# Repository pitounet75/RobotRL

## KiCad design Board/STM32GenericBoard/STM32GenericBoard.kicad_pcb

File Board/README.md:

# Robot PCB (KiCad)

KiCad projects for the RobotRL hardware.

## STM32GenericBoard

| Item | Value |
|------|--------|
| MCU (schematic) | **STM32H743VGTx** (LQFP100) — matches firmware `STM32H743VIT6` in [`RobotSTM32FirmWare.ioc`](../STM32/RobotSTM32FirmWare/RobotSTM32FirmWare.ioc) |
| IMU symbol | TDK **ICM-45686** (local lib under `libs/ICM_45686/`) |
| Status | Schematic in progress — **no routed PCB** yet (empty `.kicad_pcb`) |

### Open in KiCad

1. Open `STM32GenericBoard/STM32GenericBoard.kicad_pro`.
2. Assign footprints and complete power + bus wiring (FDCAN2, SPI1, USART, SWD).
3. Cross-check nets against CubeMX: [`STM32/RobotSTM32FirmWare/README.md`](../STM32/RobotSTM32FirmWare/README.md).

### Pin map (firmware reference)

Application CAN uses **FDCAN2** (PB12 RX, PB13 TX), not FDCAN1. See firmware README for full USART/SPI table.

### Notes

- Do not commit KiCad lock files (`~*.lck`) — listed in repo `.gitignore`.
- For symbol generation from CubeMX, tools such as [cubemx2kicad](https://github.com/alt-uranium/cubemx2kicad) can label pins from the `.ioc` file.

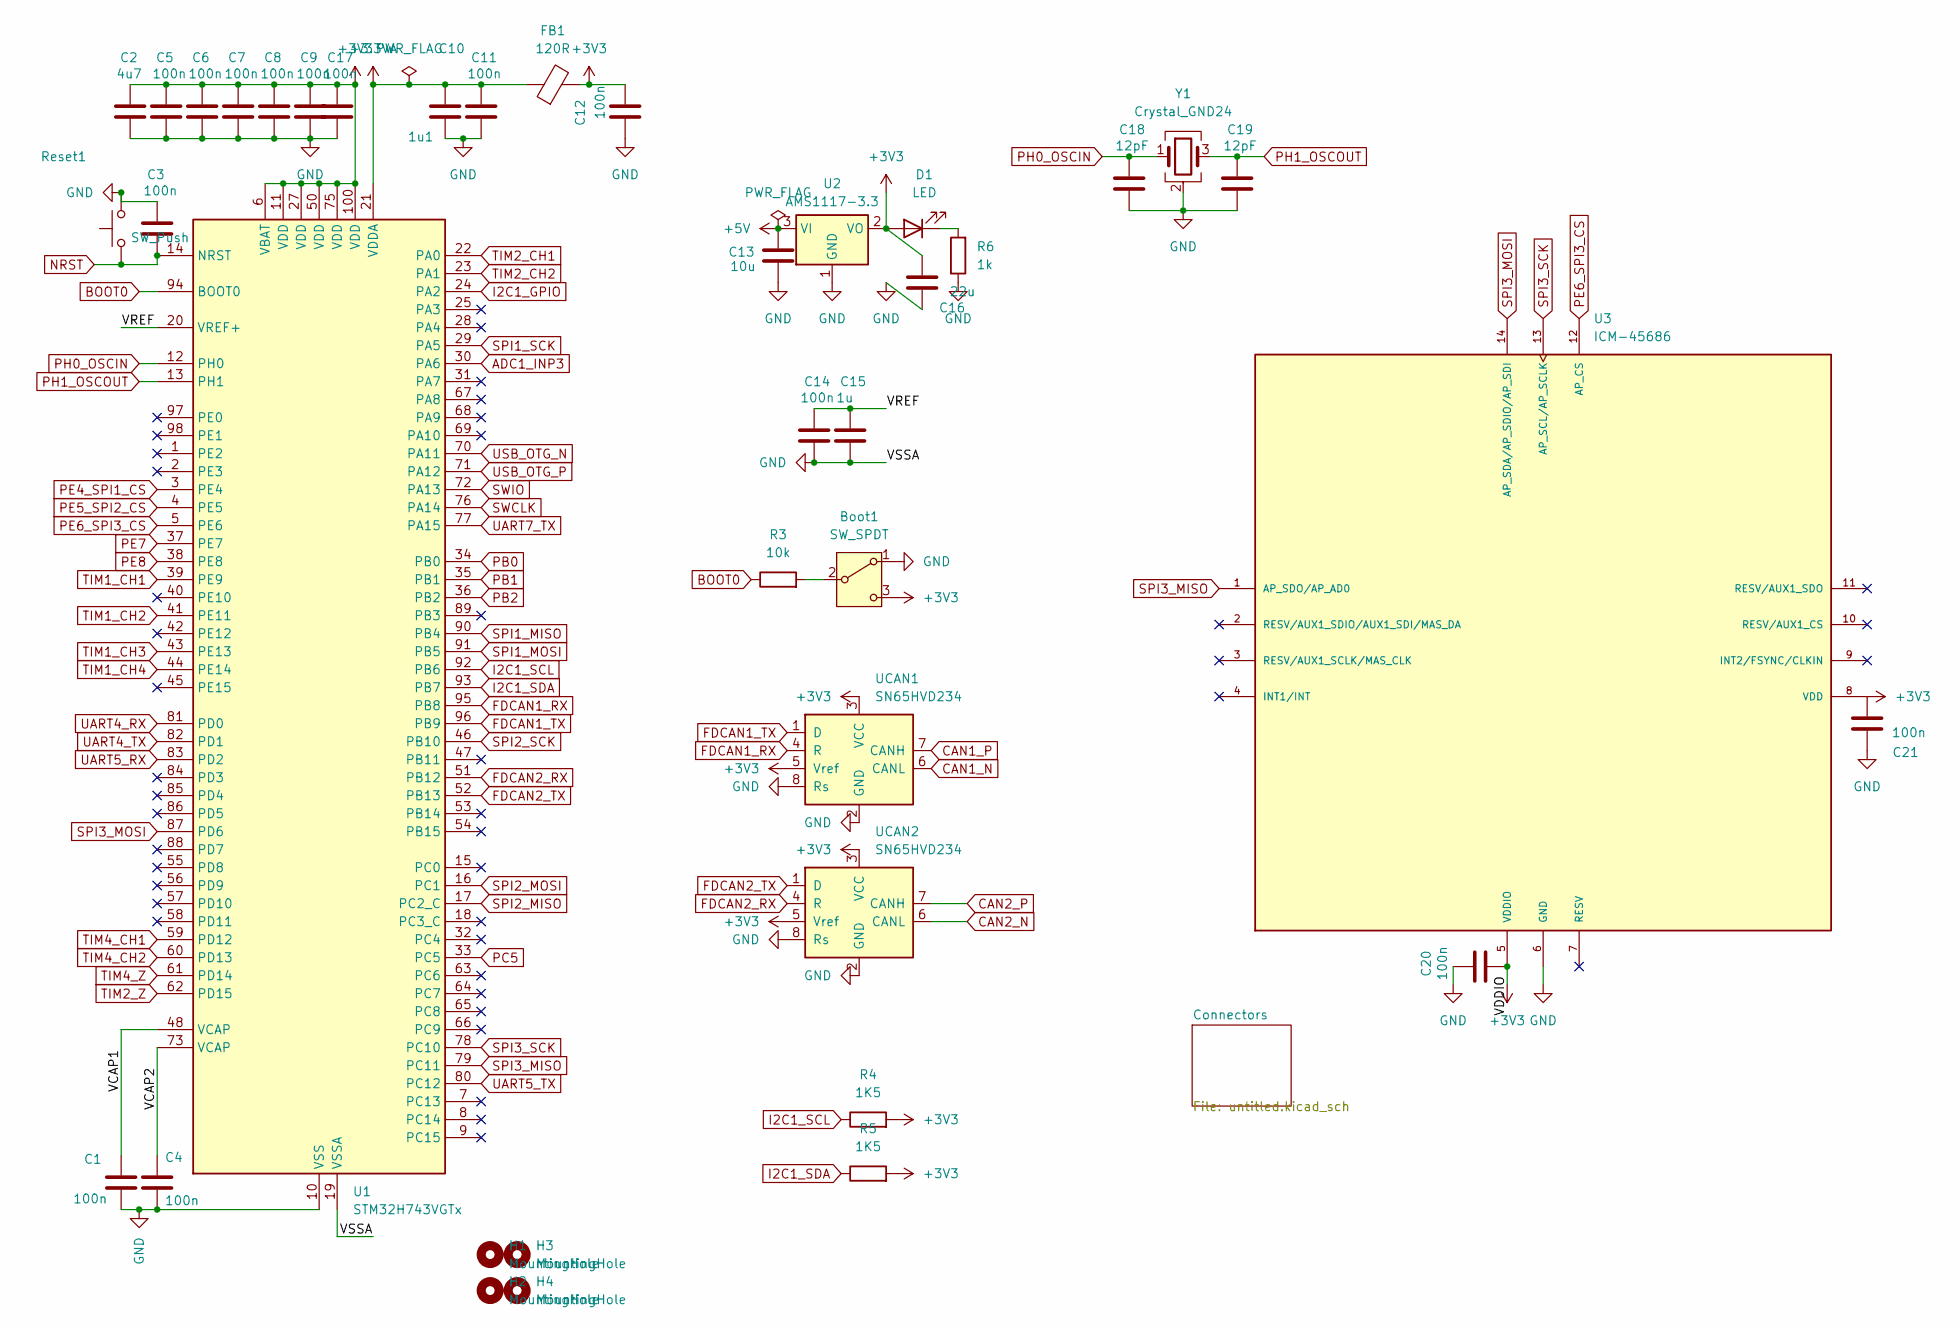
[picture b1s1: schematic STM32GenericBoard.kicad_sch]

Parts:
Boot1: SW_SPDT; SW_SPDT_PCM12
C1, C3, C4, C5, C6, C7, C8, C9, C11, C12, C14, C17, C20, C21: 100n; C_0402_1005Metric_Pad0.74x0.62mm_HandSolder
C2: 4u7; C_0603_1608Metric_Pad1.08x0.95mm_HandSolder
C10: 1u1; C_0603_1608Metric_Pad1.08x0.95mm_HandSolder
C13: 10u; C_0603_1608Metric_Pad1.08x0.95mm_HandSolder
C15: 1u; C_0603_1608Metric_Pad1.08x0.95mm_HandSolder
C16: 22u; C_0805_2012Metric_Pad1.18x1.45mm_HandSolder
C18, C19: 12pF; C_0402_1005Metric_Pad0.74x0.62mm_HandSolder
D1: LED; LED_0805_2012Metric_Pad1.15x1.40mm_HandSolder
FB1: 120R; L_0805_2012Metric_Pad1.05x1.20mm_HandSolder
H1, H2, H3, H4: MountingHole; MountingHole_2.2mm_M2
R3: 10k; R_0402_1005Metric_Pad0.72x0.64mm_HandSolder
R4, R5: 1K5; R_0402_1005Metric_Pad0.72x0.64mm_HandSolder
R6: 1k; R_0402_1005Metric_Pad0.72x0.64mm_HandSolder
Reset1: SW_Push; SW_Push_1P1T_NO_Vertical_Wuerth_434133025816
U1: STM32H743VGTx; LQFP-100_14x14mm_P0.5mm
U2: AMS1117-3.3; SOT-223-3_TabPin2
U3: ICM-45686; IC_ICM-45686; PARTREV 0.2
UCAN1, UCAN2: SN65HVD234; SOIC-8_3.9x4.9mm_P1.27mm
Y1: Crystal_GND24; Crystal_SMD_2520-4Pin_2.5x2.0mm

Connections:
+3.3VA: C10.1, C11.1, FB1.1, U1.21 (VDDA)
+3V3: Boot1.3 (C), C2.1, C5.1, C6.1, C7.1, C8.1, C9.1, C12.2, C16.1, C17.1, C20.2, C21.2, D1.2 (A), FB1.2, R4.2, R5.2, U1.6 (VBAT), U1.11 (VDD), U1.27 (VDD), U1.50 (VDD), U1.75 (VDD), U1.100 (VDD), U2.2 (VO), U3.5 (VDDIO), U3.8 (VDD), UCAN1.3 (VCC), UCAN1.5 (Vref), UCAN2.3 (VCC), UCAN2.5 (Vref); also elsewhere on the board
+5V: C13.1, U2.3 (VI); also elsewhere on the board
/VCAP1: C1.1, U1.48 (VCAP)
/VCAP2: C4.1, U1.73 (VCAP)
/VREF: C14.1, C15.1, U1.20 (VREF+)
ADC1_INP3: U1.30 (PA6); also elsewhere on the board
BOOT0: R3.1, U1.94 (BOOT0)
CAN1_N: UCAN1.6 (CANL); also elsewhere on the board
CAN1_P: UCAN1.7 (CANH); also elsewhere on the board
CAN2_N: UCAN2.6 (CANL); also elsewhere on the board
CAN2_P: UCAN2.7 (CANH); also elsewhere on the board
FDCAN1_RX: U1.95 (PB8), UCAN1.4 (R)
FDCAN1_TX: U1.96 (PB9), UCAN1.1 (D)
FDCAN2_RX: U1.51 (PB12), UCAN2.4 (R)
FDCAN2_TX: U1.52 (PB13), UCAN2.1 (D)
GND: Boot1.1 (A), C1.2, C2.2, C3.1, C4.2, C5.2, C6.2, C7.2, C8.2, C9.2, C10.2, C11.2, C12.1, C13.2, C14.2, C15.2, C16.2, C17.2, C18.2, C19.2, C20.1, C21.1, R6.1, Reset1.2, U1.10 (VSS), U1.19 (VSSA), U1.26 (VSS), U1.49 (VSS), U1.74 (VSS), U1.99 (VSS), U2.1 (GND), U3.6 (GND), UCAN1.2 (GND), UCAN1.8 (Rs), UCAN2.2 (GND), UCAN2.8 (Rs), Y1.2 (G), Y1.4 (G); also elsewhere on the board
I2C1_GPIO: U1.24 (PA2); also elsewhere on the board
I2C1_SCL: R4.1, U1.92 (PB6); also elsewhere on the board
I2C1_SDA: R5.1, U1.93 (PB7); also elsewhere on the board
NRST: C3.2, Reset1.1, U1.14 (NRST); also elsewhere on the board
unnamed: Boot1.2 (B), R3.2
unnamed: D1.1 (K), R6.2
PB0: U1.34 (PB0); also elsewhere on the board
PB1: U1.35 (PB1); also elsewhere on the board
PB2: U1.36 (PB2); also elsewhere on the board
PC5: U1.33 (PC5); also elsewhere on the board
PE4_SPI1_CS: U1.3 (PE4); also elsewhere on the board
PE5_SPI2_CS: U1.4 (PE5); also elsewhere on the board
PE6_SPI3_CS: U1.5 (PE6), U3.12 (AP_CS)
PE7: U1.37 (PE7); also elsewhere on the board
PE8: U1.38 (PE8); also elsewhere on the board
PH0_OSCIN: C18.1, U1.12 (PH0), Y1.1
PH1_OSCOUT: C19.1, U1.13 (PH1), Y1.3
SPI1_MISO: U1.90 (PB4); also elsewhere on the board
SPI1_MOSI: U1.91 (PB5); also elsewhere on the board
SPI1_SCK: U1.29 (PA5); also elsewhere on the board
SPI2_MISO: U1.17 (PC2_C); also elsewhere on the board
SPI2_MOSI: U1.16 (PC1); also elsewhere on the board
SPI2_SCK: U1.46 (PB10); also elsewhere on the board
SPI3_MISO: U1.79 (PC11), U3.1 (AP_SDO/AP_AD0)
SPI3_MOSI: U1.87 (PD6), U3.14 (AP_SDA/AP_SDIO/AP_SDI)
SPI3_SCK: U1.78 (PC10), U3.13 (AP_SCL/AP_SCLK)
SWCLK: U1.76 (PA14); also elsewhere on the board
SWIO: U1.72 (PA13); also elsewhere on the board
TIM1_CH1: U1.39 (PE9); also elsewhere on the board
TIM1_CH2: U1.41 (PE11); also elsewhere on the board
TIM1_CH3: U1.43 (PE13); also elsewhere on the board
TIM1_CH4: U1.44 (PE14); also elsewhere on the board
TIM2_CH1: U1.22 (PA0); also elsewhere on the board
TIM2_CH2: U1.23 (PA1); also elsewhere on the board
TIM2_Z: U1.62 (PD15); also elsewhere on the board
TIM4_CH1: U1.59 (PD12); also elsewhere on the board
TIM4_CH2: U1.60 (PD13); also elsewhere on the board
TIM4_Z: U1.61 (PD14); also elsewhere on the board
UART4_RX: U1.81 (PD0); also elsewhere on the board
UART4_TX: U1.82 (PD1); also elsewhere on the board
UART5_RX: U1.83 (PD2); also elsewhere on the board
UART5_TX: U1.80 (PC12); also elsewhere on the board
UART7_TX: U1.77 (PA15); also elsewhere on the board
USB_OTG_N: U1.70 (PA11); also elsewhere on the board
USB_OTG_P: U1.71 (PA12); also elsewhere on the board

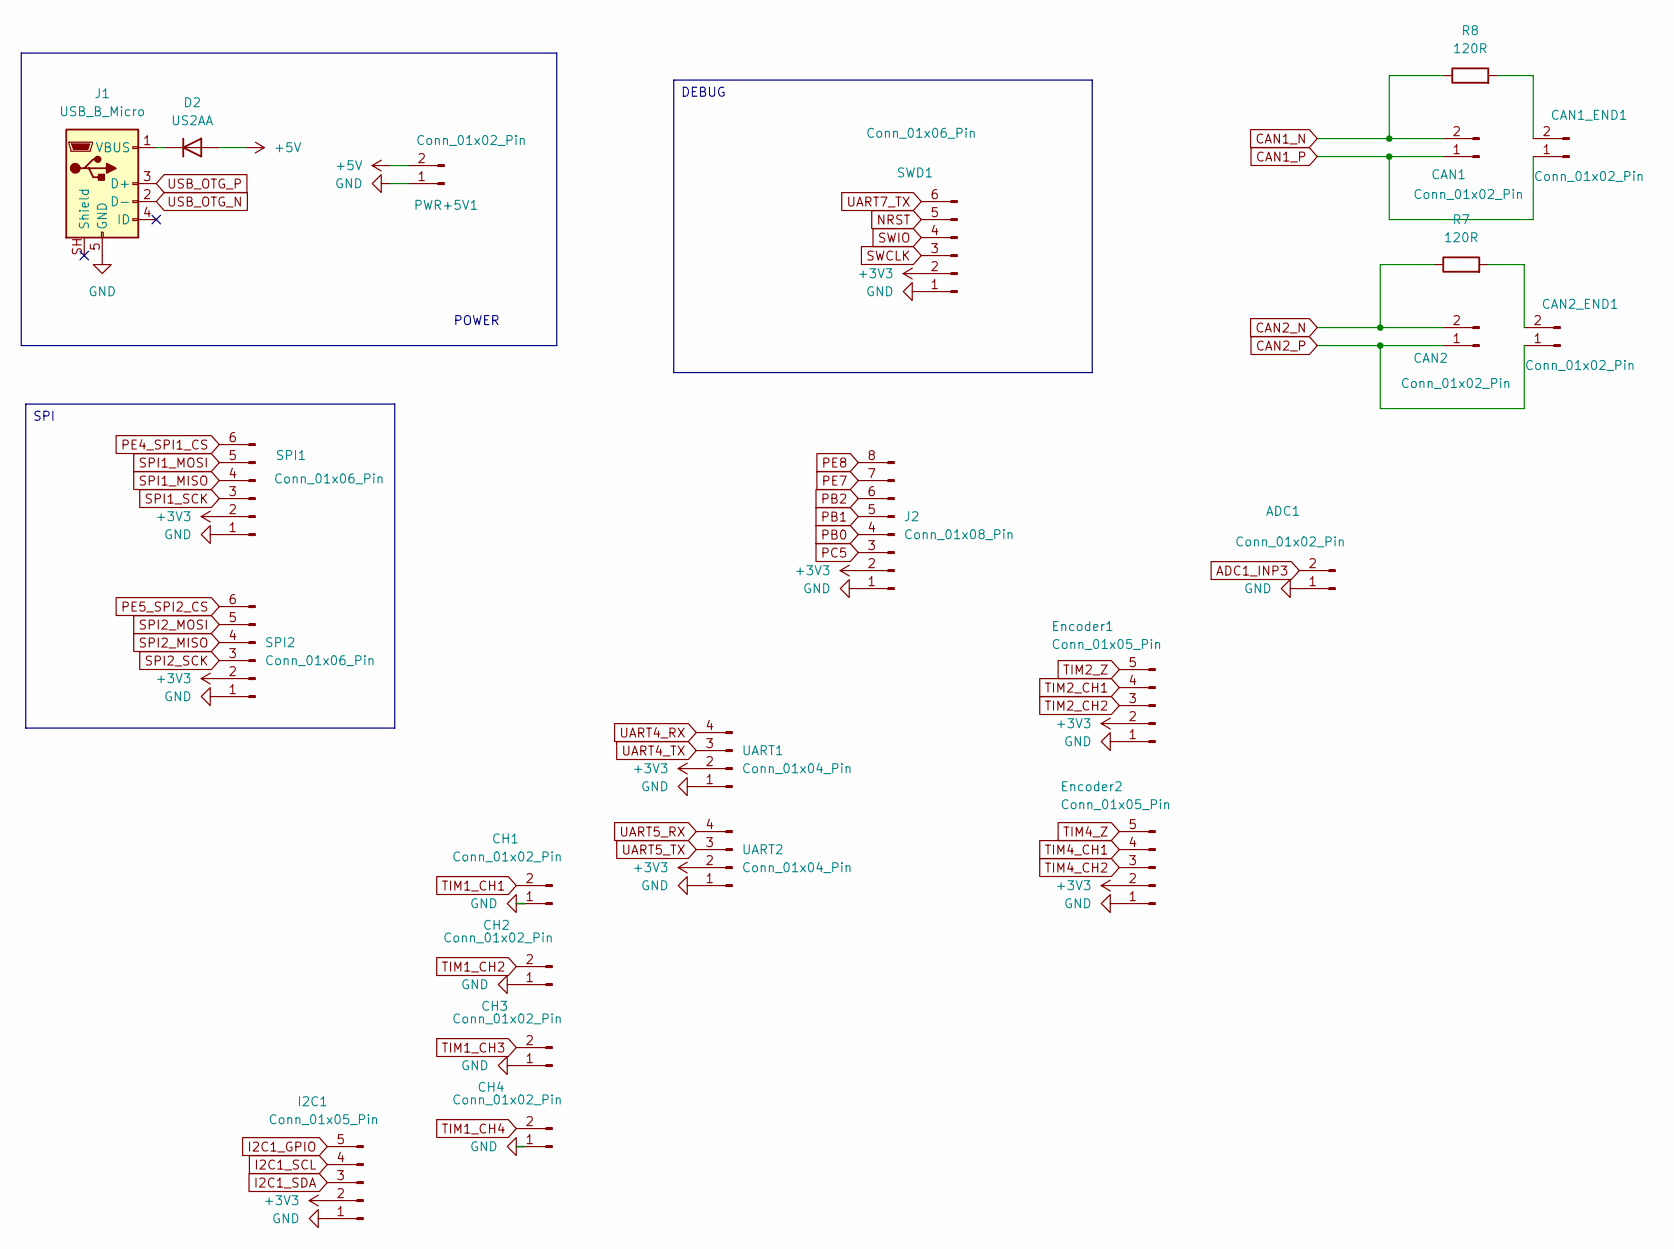
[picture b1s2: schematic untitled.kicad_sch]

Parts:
ADC1: Conn_01x02_Pin; JST_GH_BM02B-GHS-TBT_1x02-1MP_P1.25mm_Vertical
CAN1, CAN2: Conn_01x02_Pin; JST_GH_BM02B-GHS-TBT_1x02-1MP_P1.25mm_Vertical
CAN1_END1, CAN2_END1: Conn_01x02_Pin; PinHeader_1x02_P2.54mm_Vertical
CH1, CH2, CH3, CH4: Conn_01x02_Pin; JST_GH_BM02B-GHS-TBT_1x02-1MP_P1.25mm_Vertical
D2: US2AA; D_SMA
Encoder1, Encoder2: Conn_01x05_Pin; JST_GH_BM05B-GHS-TBT_1x05-1MP_P1.25mm_Vertical
I2C1: Conn_01x05_Pin; JST_GH_BM05B-GHS-TBT_1x05-1MP_P1.25mm_Vertical
J1: USB_B_Micro; USB_Micro-B_Amphenol_10118194-0001LF_Horizontal
J2: Conn_01x08_Pin; JST_GH_BM08B-GHS-TBT_1x08-1MP_P1.25mm_Vertical
PWR+5V1: Conn_01x02_Pin; PinHeader_1x02_P2.54mm_Vertical
R7, R8: 120R; R_0402_1005Metric_Pad0.72x0.64mm_HandSolder
SPI1, SPI2: Conn_01x06_Pin; JST_GH_BM06B-GHS-TBT_1x06-1MP_P1.25mm_Vertical
SWD1: Conn_01x06_Pin; JST_GH_BM06B-GHS-TBT_1x06-1MP_P1.25mm_Vertical
UART1, UART2: Conn_01x04_Pin; JST_GH_BM04B-GHS-TBT_1x04-1MP_P1.25mm_Vertical

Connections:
+3V3: Encoder1.2, Encoder2.2, I2C1.2, J2.2, SPI1.2, SPI2.2, SWD1.2, UART1.2, UART2.2; also elsewhere on the board
+5V: D2.2 (A), PWR+5V1.2; also elsewhere on the board
ADC1_INP3: ADC1.2; also elsewhere on the board
CAN1_N: CAN1.2, R8.1; also elsewhere on the board
CAN1_P: CAN1.1, CAN1_END1.1; also elsewhere on the board
CAN2_N: CAN2.2, R7.1; also elsewhere on the board
CAN2_P: CAN2.1, CAN2_END1.1; also elsewhere on the board
GND: ADC1.1, CH1.1, CH2.1, CH3.1, CH4.1, Encoder1.1, Encoder2.1, I2C1.1, J1.5 (GND), J2.1, PWR+5V1.1, SPI1.1, SPI2.1, SWD1.1, UART1.1, UART2.1; also elsewhere on the board
I2C1_GPIO: I2C1.5; also elsewhere on the board
I2C1_SCL: I2C1.4; also elsewhere on the board
I2C1_SDA: I2C1.3; also elsewhere on the board
NRST: SWD1.5; also elsewhere on the board
unnamed: CAN1_END1.2, R8.2
unnamed: CAN2_END1.2, R7.2
unnamed: D2.1 (K), J1.1 (VBUS)
PB0: J2.4; also elsewhere on the board
PB1: J2.5; also elsewhere on the board
PB2: J2.6; also elsewhere on the board
PC5: J2.3; also elsewhere on the board
PE4_SPI1_CS: SPI1.6; also elsewhere on the board
PE5_SPI2_CS: SPI2.6; also elsewhere on the board
PE7: J2.7; also elsewhere on the board
PE8: J2.8; also elsewhere on the board
SPI1_MISO: SPI1.4; also elsewhere on the board
SPI1_MOSI: SPI1.5; also elsewhere on the board
SPI1_SCK: SPI1.3; also elsewhere on the board
SPI2_MISO: SPI2.4; also elsewhere on the board
SPI2_MOSI: SPI2.5; also elsewhere on the board
SPI2_SCK: SPI2.3; also elsewhere on the board
SWCLK: SWD1.3; also elsewhere on the board
SWIO: SWD1.4; also elsewhere on the board
TIM1_CH1: CH1.2; also elsewhere on the board
TIM1_CH2: CH2.2; also elsewhere on the board
TIM1_CH3: CH3.2; also elsewhere on the board
TIM1_CH4: CH4.2; also elsewhere on the board
TIM2_CH1: Encoder1.4; also elsewhere on the board
TIM2_CH2: Encoder1.3; also elsewhere on the board
TIM2_Z: Encoder1.5; also elsewhere on the board
TIM4_CH1: Encoder2.4; also elsewhere on the board
TIM4_CH2: Encoder2.3; also elsewhere on the board
TIM4_Z: Encoder2.5; also elsewhere on the board
UART4_RX: UART1.4; also elsewhere on the board
UART4_TX: UART1.3; also elsewhere on the board
UART5_RX: UART2.4; also elsewhere on the board
UART5_TX: UART2.3; also elsewhere on the board
UART7_TX: SWD1.6; also elsewhere on the board
USB_OTG_N: J1.2 (D-); also elsewhere on the board
USB_OTG_P: J1.3 (D+); also elsewhere on the board

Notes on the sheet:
POWER
SPI
DEBUG

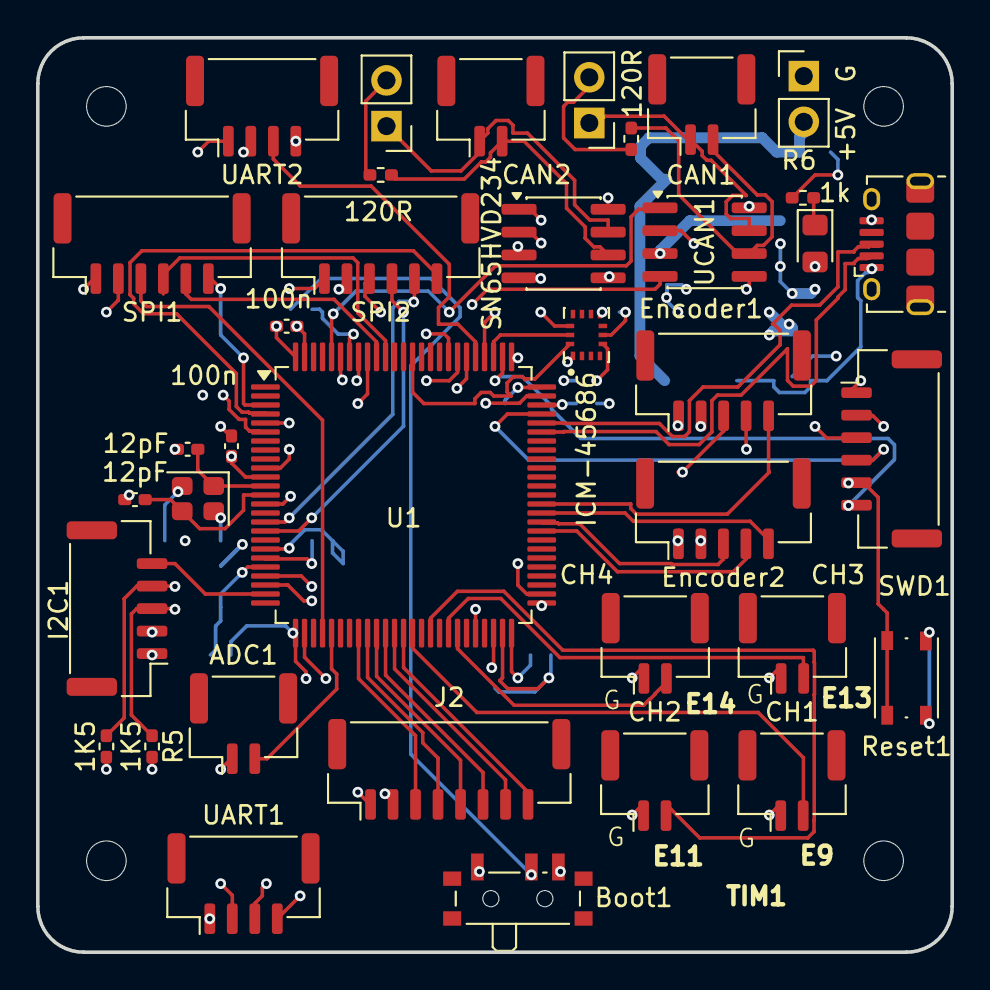
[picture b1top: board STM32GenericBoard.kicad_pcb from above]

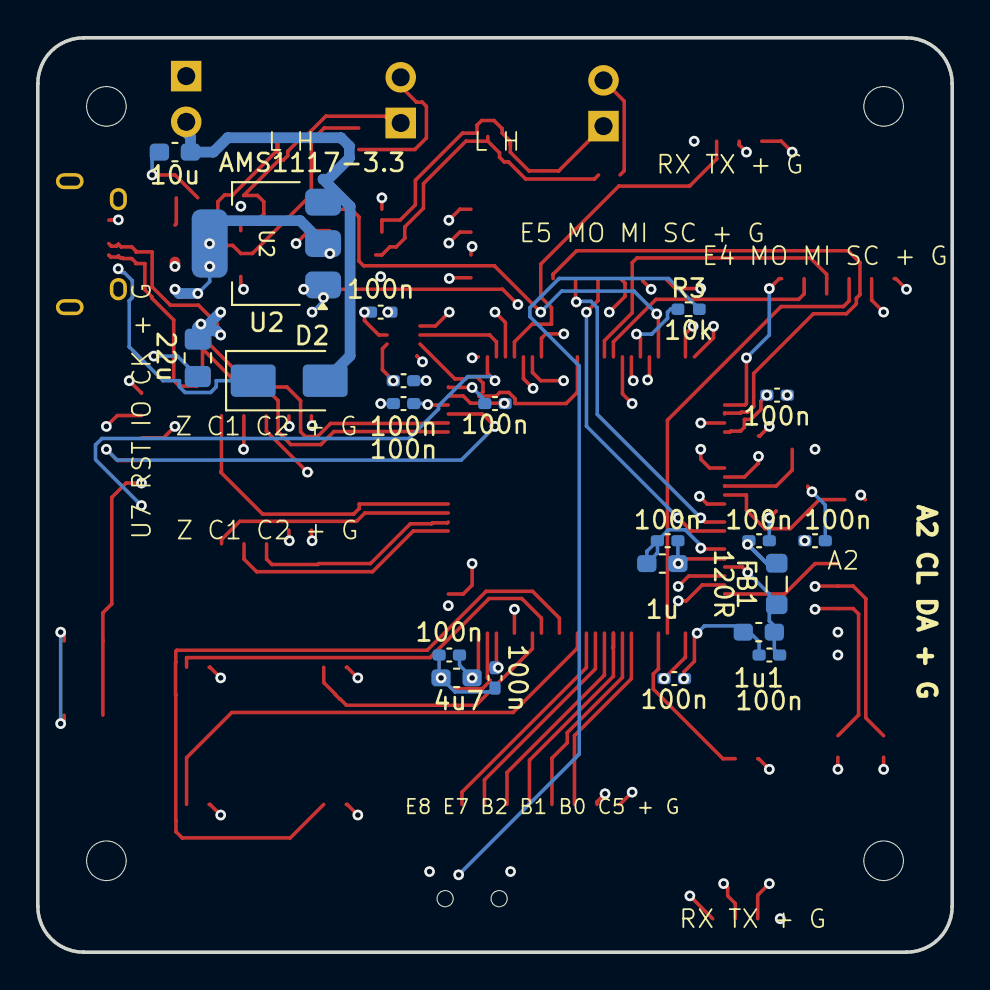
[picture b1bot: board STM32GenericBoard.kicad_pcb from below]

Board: 6 copper layers, 50.8 x 50.8 mm, 62 parts (21 on the bottom side), 65 nets.

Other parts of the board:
+5V: Conn_01x02_Pin; PinHeader_1x02_P2.54mm_Vertical

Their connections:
+5V: +5V.2; also elsewhere on the board
GND: +5V.1; also elsewhere on the board

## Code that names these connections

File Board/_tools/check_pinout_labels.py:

#!/usr/bin/env python3
"""Compare KiCad schematic net labels on U5 vs STM32H743LFQP100Pinout.ioc."""
import re
from pathlib import Path

ROOT = Path(__file__).resolve().parents[1]
IOC = ROOT / "STM32H743LFQP100Pinout" / "STM32H743LFQP100Pinout.ioc"
SCH = ROOT / "STM32GenericBoard" / "STM32GenericBoard.kicad_sch"


def parse_ioc(path: Path) -> dict[str, str]:
    text = path.read_text(encoding="utf-8", errors="replace")
    pins: dict[str, str] = {}
    for line in text.splitlines():
        if ".Signal=" not in line or not line[0].isalpha():
            continue
        port_part, sig = line.split(".Signal=", 1)
        raw = port_part.strip().replace("\\\\", "")
        if "PH0" in raw:
            port = "PH0"
        elif "PH1" in raw:
            port = "PH1"
        elif raw.startswith("PA13"):
            port = "PA13"
        elif raw.startswith("PA14"):
            port = "PA14"
        elif raw.startswith("PA15"):
            port = "PA15"
        elif raw.startswith("PB3"):
            port = "PB3"
        elif raw.startswith("PB4"):
            port = "PB4"
        else:
            port = raw.split("(")[0].split("-")[0]
        pins[port] = sig.strip()
    return pins


LABEL_TO_PORT = {
    "PH0_OSCIN": "PH0",
    "PH1_OSCOUT": "PH1",
    "SWIO": "PA13",
    "SWCLK": "PA14",
    "SWO": "PB3",
    "UART4_TX": "PA0",
    "UART4_RX": "PD0",
    "UART5_TX": "PC12",
    "UART5_RX": "PD2",
    "SPI1_SCK": "PA5",
    "SPI1_MOSI": "PB5",
    "SPI1_MISO": "PB4",
    "SPI1_MSIO": "PB4",  # typo on schematic
    "SPI2_SCK": "PB10",
    "SPI2_MOSI": "PC1",
    "SPI2_MISO": "PC2_C",
    "FDCAN2_RX": "PB12",
    "FDCAN2_TX": "PB13",
    "FDCAN1_RX": "PB8",
    "FDCAN1_TX": "PD1",
    "I2C1_SCL": "PB6",
    "I2C1_SDA": "PB7",
    "USB_OTG_DM": "PA11",
    "USB_OTG_DP": "PA12",
    "TIM2_CH1": "PA15",
    "TIM2_CH2": "PA1",
    "TIM4_CH1": "PD12",
    "TIM4_CH2": "PD13",
    "TIM1_CH1": "PE9",
    "TIM1_CH2": "PE11",
    "TIM1_CH3": "PE13",
    "TIM1_CH4": "PE14",
    "PB0": "PB0",
    "PB1": "PB1",
    "PB2": "PB2",
    "PC5": "PC5",
    "PE7": "PE7",
    "PE8": "PE8",
    "PE4_SPI1_CS": "PE4",
    "PE5_SPI1_CS": "PE5",
    "PE6_SPI2_CS": "PE6",
    "SPI3_SCK": "PC10",
    "SPI3_MOSI": "PC11",
    "SPI3_MISO": "PC12",
}


def expected_port(label: str):
    if label in LABEL_TO_PORT:
        return LABEL_TO_PORT[label]
    m = re.match(r"^(P[A-Z][0-9]+(?:_C)?)$", label)
    if m:
        return m.group(1)
    return None


def main() -> None:
    ioc_pins = parse_ioc(IOC)
    sch = SCH.read_text(encoding="utf-8", errors="replace")
    labels = sorted(set(re.findall(r'\(label "([^"]+)"', sch)))

    print("=== IOC configured pins ===")
    for p in sorted(ioc_pins):
        print(f"  {p}: {ioc_pins[p]}")

    ok: list[tuple[str, str, str]] = []
    wrong: list[tuple[str, str, str]] = []
    unmapped: list[str] = []
    skip_power = {"VSSA", "VREF", "BOOT0", "+3V3", "GND"}

    for label in labels:
        if label in skip_power:
            continue
        port = expected_port(label)
        if port is None:
            unmapped.append(label)
            continue
        if port not in ioc_pins:
            wrong.append((label, port, "GPIO not configured in pinout IOC"))
        else:
            ok.append((label, port, ioc_pins[port]))

    print(f"\n=== OK ({len(ok)}) ===")
    for row in ok:
        print(f"  {row[0]} -> {row[1]} ({row[2]})")

    typos = [l for l in labels if "MSIO" in l]
    spi3 = [l for l in labels if "SPI3" in l]
    cs = [l for l in labels if "CS" in l or "_SPI" in l]

    print("\n=== Problems ===")
    if typos:
        print(f"  Typo: {typos} -> rename to SPI1_MISO")
    if spi3:
        print(f"  SPI3 labels not in pinout IOC: {spi3}")
        print("    (PC10/11/12 conflict: PC12 is UART5_TX in IOC)")
    if cs:
        for l in cs:
            p = expected_port(l)
            print(f"  CS label {l} on {p}: not in pinout IOC (add GPIO_Output in Cube if used)")
    for row in wrong:
        print(f"  {row[0]} -> {row[1]}: {row[2]}")
    if unmapped:
        print(f"  Unmapped labels: {unmapped}")

    labeled_ports = {expected_port(l) for l in labels if expected_port(l)}
    print("\n=== IOC pins without function label on schematic ===")
    for p, s in sorted(ioc_pins.items()):
        if p in labeled_ports:
            continue
        if p in {"PB0", "PB1", "PB2", "PC5", "PE7", "PE8"}:
            note = "GPIO_Input — optional to use port name as label"
        elif p == "PA6":
            note = "ADC1_INP3 — consider ADC label"
        elif p == "PA10":
            note = "USB_OTG_FS_ID — consider USB_OTG_ID label"
        else:
            note = "missing label"
        print(f"  {p}: {s} ({note})")


if __name__ == "__main__":
    main()

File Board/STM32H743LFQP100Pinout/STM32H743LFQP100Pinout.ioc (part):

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Mcu.Name=STM32H743VGTx
Mcu.Package=LQFP100
Mcu.UserName=STM32H743VGTx
PA0.Signal=S_TIM2_CH1_ETR
PA1.Signal=S_TIM2_CH2
PA11.Mode=Device_Only
PA11.Signal=USB_OTG_FS_DM
PA12.Mode=Device_Only
PA12.Signal=USB_OTG_FS_DP
PA13\ (JTMS/SWDIO).Mode=Trace_Asynchronous_SW
PA13\ (JTMS/SWDIO).Signal=DEBUG_JTMS-SWDIO
PA14\ (JTCK/SWCLK).Mode=Trace_Asynchronous_SW
PA14\ (JTCK/SWCLK).Signal=DEBUG_JTCK-SWCLK
PA15\ (JTDI).Mode=Asynchronous
PA15\ (JTDI).Signal=UART7_TX
PA2.GPIOParameters=GPIO_Label
PA2.GPIO_Label=I2C1_GPIO
PA2.Signal=GPIO_Output
PA5.Mode=Full_Duplex_Master
PA5.Signal=SPI1_SCK
PA6.Signal=ADCx_INP3
PA8.Mode=Asynchronous
PA8.Signal=UART7_RX
PB0.Signal=GPIO_Input
PB1.Signal=GPIO_Input
PB10.Mode=Full_Duplex_Master
PB10.Signal=SPI2_SCK
PB12.Mode=FDCAN_Activate
PB12.Signal=FDCAN2_RX
PB13.Mode=FDCAN_Activate
PB13.Signal=FDCAN2_TX
PB2.Signal=GPIO_Input
PB3\ (JTDO/TRACESWO).Mode=Trace_Asynchronous_SW
PB3\ (JTDO/TRACESWO).Signal=DEBUG_JTDO-SWO
PB4\ (NJTRST).Mode=Full_Duplex_Master
PB4\ (NJTRST).Signal=SPI1_MISO
PB5.Mode=Full_Duplex_Master
PB5.Signal=SPI1_MOSI
PB6.Mode=I2C
PB6.Signal=I2C1_SCL
PB7.Mode=I2C
PB7.Signal=I2C1_SDA
PB8.Mode=FDCAN_Activate
PB8.Signal=FDCAN1_RX
PB9.Mode=FDCAN_Activate
PB9.Signal=FDCAN1_TX
PC1.Mode=Full_Duplex_Master
PC1.Signal=SPI2_MOSI
PC10.Mode=Full_Duplex_Master
PC10.Signal=SPI3_SCK
PC11.Mode=Full_Duplex_Master
PC11.Signal=SPI3_MISO
PC12.Mode=Asynchronous
PC12.Signal=UART5_TX
PC14-OSC32_IN\ (OSC32_IN).Mode=LSE-External-Oscillator
PC14-OSC32_IN\ (OSC32_IN).Signal=RCC_OSC32_IN
PC15-OSC32_OUT\ (OSC32_OUT).Mode=LSE-External-Oscillator
PC15-OSC32_OUT\ (OSC32_OUT).Signal=RCC_OSC32_OUT
PC2_C.Mode=Full_Duplex_Master
PC2_C.Signal=SPI2_MISO
PC5.GPIOParameters=PinAttribute
PC5.PinAttribute=Free
PC5.Signal=GPIO_Input
PD0.Mode=Asynchronous
PD0.Signal=UART4_RX
PD1.Mode=Asynchronous
PD1.Signal=UART4_TX
PD12.Signal=S_TIM4_CH1
PD13.Signal=S_TIM4_CH2
PD14.GPIOParameters=GPIO_Label
PD14.GPIO_Label=TIM4_Z
PD14.Signal=GPIO_Input
PD15.GPIOParameters=GPIO_Label
PD15.GPIO_Label=TIM2_Z
PD15.Signal=GPIO_Input
PD2.Mode=Asynchronous
PD2.Signal=UART5_RX
PD6.Mode=Full_Duplex_Master
PD6.Signal=SPI3_MOSI
PE11.Signal=S_TIM1_CH2
PE13.Signal=S_TIM1_CH3
PE14.Signal=S_TIM1_CH4
PE4.GPIOParameters=GPIO_Label
PE4.GPIO_Label=PE4_SPI1_CS
PE4.Signal=GPIO_Output
PE5.GPIOParameters=GPIO_Label
PE5.GPIO_Label=PE5_SPI2_CS
PE5.Signal=GPIO_Output
PE6.GPIOParameters=GPIO_Label
PE6.GPIO_Label=PE6_SPI3_CS
PE6.Signal=GPIO_Output
PE7.Signal=GPIO_Input
PE8.Signal=GPIO_Input
PE9.GPIOParameters=PinAttribute
PE9.PinAttribute=Free
PE9.Signal=S_TIM1_CH1
RCC.HSE_VALUE=16000000
RCC.SYSCLKFreq_VALUE=480000000
RCC.SYSCLKSource=RCC_SYSCLKSOURCE_PLLCLK
board=custom

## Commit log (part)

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2026-03-09 feat: add RobotRL project with two_wheeler task and hardware modules
    Made-with: Cursor
2026-03-09 refactor: remove duplicate root-level two_wheeler files
    Made-with: Cursor
2026-03-16 chore: add Cursor rules (.mdc) for agents and git preferences
    Made-with: Cursor
2026-03-27 Add STM32 stub, sweep_param script, update RSL-RL cfg and training agent rules
    Made-with: Cursor
2026-04-05 Add firmware
2026-05-12 Update firmware and enhance training agent configurations
2026-06-01 Save board
2026-06-03 save
